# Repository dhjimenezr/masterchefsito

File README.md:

# MASTERCHEFSITO

## Autores
- David Jiménez Rodríguez
- Camilo Rodríguez Navarrete

## Descripción del producto

A.	Denominación del Proyecto.

Sistema que permite al usuario tener una interacción con los ingredientes o alimentos disponibles en una despensa, elaborado por estudiantes de pregrado de la Universidad Nacional de Colombia en el marco de Proyecto Académico.

B.	Descripción del Proyecto.

Diseño de un sistema que permita la captura de imágenes e identificación de algunos productos alimenticios dentro de la cocina, que permita tener un control de las características fundamentales de dichos productos como fecha de caducidad, temperatura apropiada para la conservación del mismo, disponibilidad y de manera anexa algunas posibles recetas o utilidades. 

C.	Fundamentación o Justificación.
El mundo actual lleva a que la rutina social, laboral o académica impida que algunas personas se acerquen al mundo culinario o gastronómico de forma que represente un bienestar, además de la cantidad de desperdicio o mal uso que se les dan a algunos productos alimenticios. 
Nuestro diseño le permitirá al usuario tener un mejor control de los alimentos que dispone o consume regularmente, sin necesidad de disponer de su tiempo cotidiano para este fin. Todo esto con una manera simple de implementar para que este al alcance de cualquier persona. 
D.	Marco Institucional. 

El sistema es planteado, desarrollado y presentado por estudiantes de la Universidad Nacional de Colombia, pertenecientes al programa de pregrado de Ingeniería Electrónica haciendo parte del proyecto final de la materia Sistemas Embebidos. Por lo anterior se siguen las directrices dadas por la metodología de la materia impartida por el docente. 

E.	Finalidad del Proyecto
a.	Lograr una optimización del tiempo empleado por el usuario para obtener un registro de los productos alimenticios que posee en su despensa y el uso que le puede dar a ellos.
b.	Generar una mejora en el valor nutricional en la alimentación diaria del usuario.
c.	Mejorar el aprovechamiento de los productos disponibles teniendo un mejor control en sus fechas de caducidad respectivas, llegando a disminuir los índices de desperdicio dentro de una cocina. 

F.	Objetivos.

Objetivo General: Realizar un sistema que permita identificar los ingredientes alimenticios dentro de una cómoda o nevera, con el fin de poder generar una administración de los productos e identificar recetas culinarias que se puedan hacer con los mismos. 

Objetivos Específicos:

a.	Captar imágenes de los alimentos e identificarlos.
b.	Crear un servidor y base de datos con información de la fecha de vencimiento y recetario de los productos.
c.	Aplicación que permita visualizar la información del sistema.
d.	Registro de la caducidad de los alimentos.
e.	Selección de alimentos preferidos y disponibilidad de estos.

G.	Estudiantes del Grupo. 

El grupo de trabajo esta conformado por los siguientes estudiantes de la asignatura:
David Hermando Jiménez Rodríguez
Camilo Andrés Rodríguez Navarrete

H.	Actividades y Tareas.

a.	Acoplamiento de Periféricos a microcontrolador.
b.	Acoplamiento de la Cámara por medio del microcontrolador.
c.	Diseño del prototipo físico.
d.	Acoplamiento del sistema.

I.	Recursos.

Recursos Materiales
•	Microcontrolador ESP32.
•	Celda de Carga.
•	Display.
•	Buzzer.

Recursos Técnicos
•	Programación en Micro Phyton.

Recursos Humanos
•	David Hermando Jiménez Rodríguez: Desarrollador de microcontroladores.
•	Camilo Andrés Rodríguez Navarrete: Desarrollador de aplicaciones y prototipos físicos.  

J.	Presupuesto.
Característica	Precio
Materiales 	$ 600.000,00
Mano de Obra 	$ 1.500.00,00
Costos Fijos	$ 400.000
Total	$ 2.500.000,00

## Periféricos a trabajar

- Pantalla LCD PCD8544
- Celda de carga
- Sensor de temperatura digital DS18B20
- Teclado matrix 3x3

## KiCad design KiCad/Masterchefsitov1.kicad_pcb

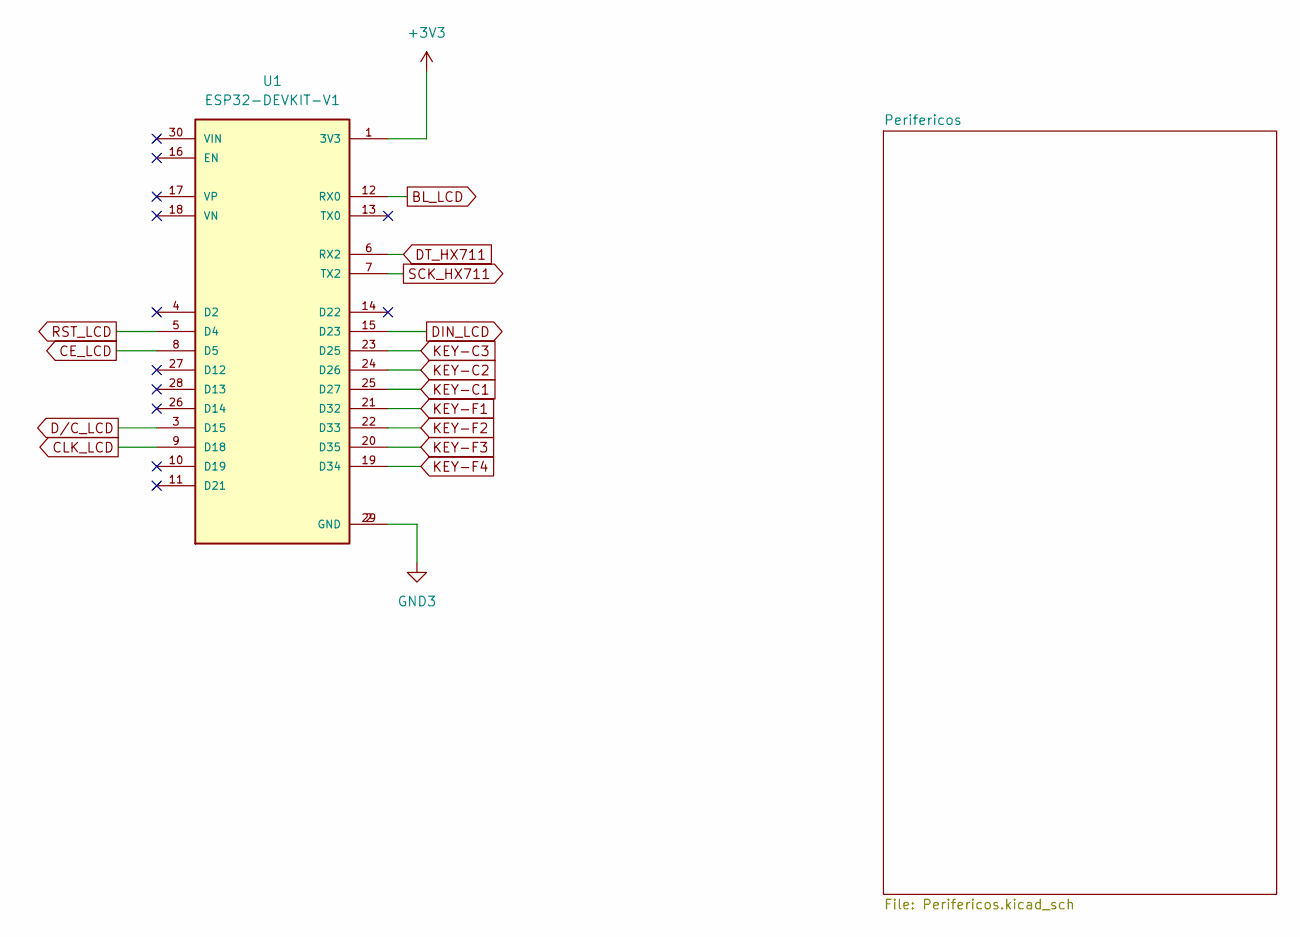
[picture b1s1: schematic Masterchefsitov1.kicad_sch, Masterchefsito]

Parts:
U1: ESP32-DEVKIT-V1; MODULE_ESP32_DEVKIT_V1; PARTREV N/A

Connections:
+3V3: U1.1 (3V3); also elsewhere on the board
BL_LCD: U1.12 (RX0); also elsewhere on the board
CE_LCD: U1.8 (D5); also elsewhere on the board
CLK_LCD: U1.9 (D18); also elsewhere on the board
DIN_LCD: U1.15 (D23); also elsewhere on the board
DT_HX711: U1.6 (RX2); also elsewhere on the board
D/C_LCD: U1.3 (D15); also elsewhere on the board
GND3: U1.2 (GND), U1.29 (GND); also elsewhere on the board
KEY-C1: U1.25 (D27); also elsewhere on the board
KEY-C2: U1.24 (D26); also elsewhere on the board
KEY-C3: U1.23 (D25); also elsewhere on the board
KEY-F1: U1.21 (D32); also elsewhere on the board
KEY-F2: U1.22 (D33); also elsewhere on the board
KEY-F3: U1.20 (D35); also elsewhere on the board
KEY-F4: U1.19 (D34); also elsewhere on the board
RST_LCD: U1.5 (D4); also elsewhere on the board
SCK_HX711: U1.7 (TX2); also elsewhere on the board

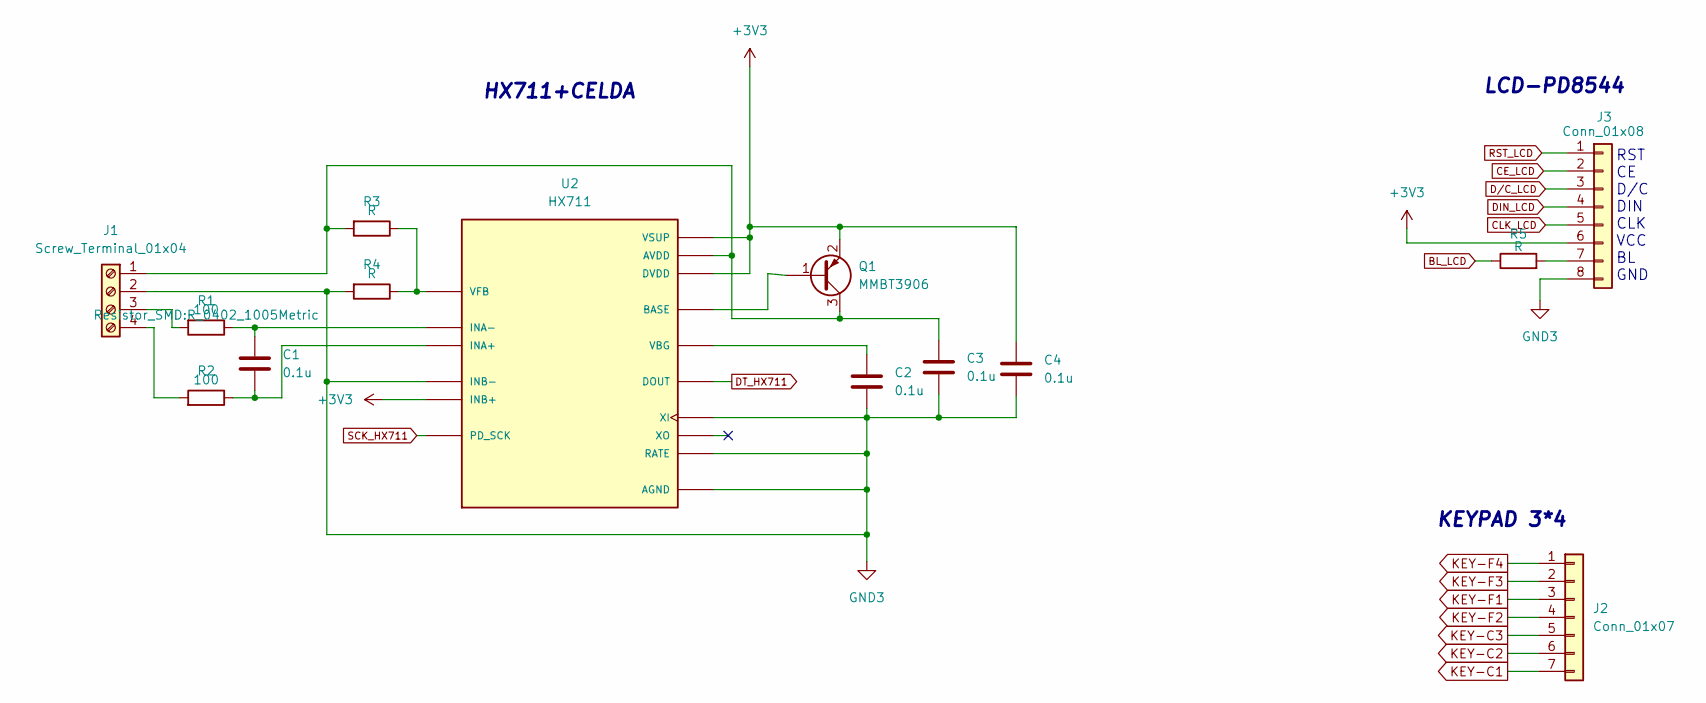
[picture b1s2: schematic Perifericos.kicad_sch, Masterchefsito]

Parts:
C1, C2, C3, C4: 0.1u; C_0201_0603Metric
J1: Screw_Terminal_01x04; TerminalBlock_bornier-4_P5.08mm
J2: Conn_01x07; TerminalBlock_4Ucon_1x07_P3.50mm_Horizontal
J3: Conn_01x08; Adafruit_SSD1306
Q1: MMBT3906; SOT-23
R1: 100; R_0402_1005Metric
R2: 100; R_0402_1005Metric_Pad0.72x0.64mm_HandSolder
R3, R4, R5: R; R_0402_1005Metric
U2: HX711; SOP127P600X180-16N; PARTREV V2.0

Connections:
+3V3: C4.1, J3.6, Q1.2 (E), U2.1 (VSUP), U2.10 (INB+), U2.16 (DVDD); also elsewhere on the board
BL_LCD: R5.1; also elsewhere on the board
CE_LCD: J3.2; also elsewhere on the board
CLK_LCD: J3.5; also elsewhere on the board
DIN_LCD: J3.4; also elsewhere on the board
DT_HX711: U2.12 (DOUT); also elsewhere on the board
D/C_LCD: J3.3; also elsewhere on the board
GND3: C2.2, C3.2, C4.2, J1.2, J3.8, R4.2, U2.5 (AGND), U2.9 (INB-), U2.14 (XI), U2.15 (RATE); also elsewhere on the board
KEY-C1: J2.7; also elsewhere on the board
KEY-C2: J2.6; also elsewhere on the board
KEY-C3: J2.5; also elsewhere on the board
KEY-F1: J2.3; also elsewhere on the board
KEY-F2: J2.4; also elsewhere on the board
KEY-F3: J2.2; also elsewhere on the board
KEY-F4: J2.1; also elsewhere on the board
unnamed: C1.1, R1.1, U2.7 (INA-)
unnamed: C1.2, R2.1, U2.8 (INA+)
unnamed: C2.1, U2.6 (VBG)
unnamed: C3.1, J1.1, Q1.3 (C), R3.2, U2.3 (AVDD)
unnamed: J1.3, R1.2
unnamed: J1.4, R2.2
unnamed: J3.7, R5.2
unnamed: Q1.1 (B), U2.2 (BASE)
unnamed: R3.1, R4.1, U2.4 (VFB)
RST_LCD: J3.1; also elsewhere on the board
SCK_HX711: U2.11 (PD_SCK); also elsewhere on the board

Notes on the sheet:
LCD-PD8544
RST CE D/C DIN CLK VCC BL GND
HX711+CELDA
KEYPAD 3*4

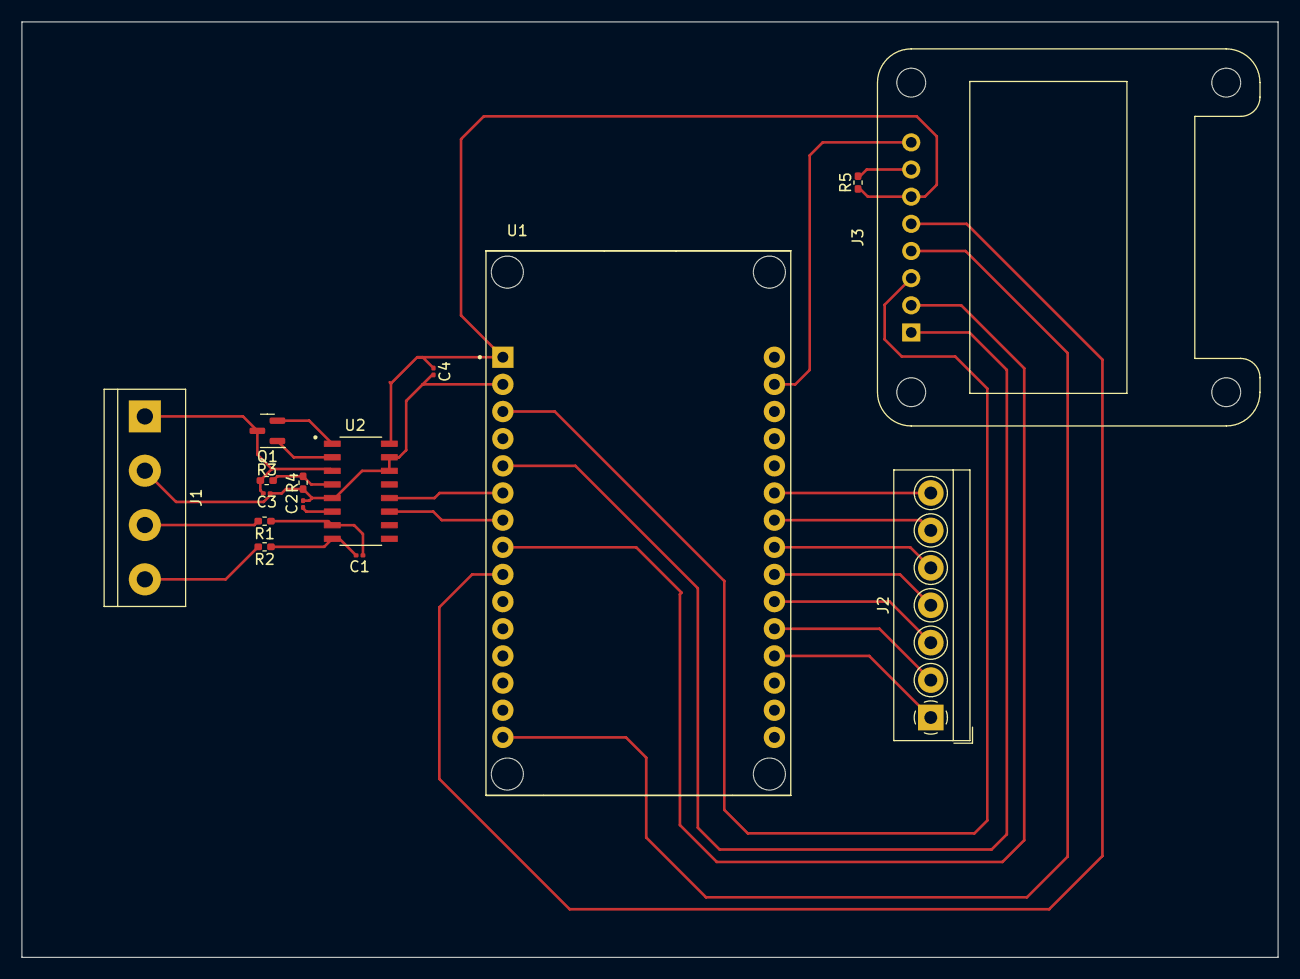
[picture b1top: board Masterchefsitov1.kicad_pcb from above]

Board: 2 copper layers, 117.5 x 87.5 mm, 15 parts (0 on the bottom side), 26 nets.

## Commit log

2022-07-27 Librerias kicad
2022-07-28 LCD TEST
2022-07-28 Readme update
2022-08-02 Bloque+PCB
